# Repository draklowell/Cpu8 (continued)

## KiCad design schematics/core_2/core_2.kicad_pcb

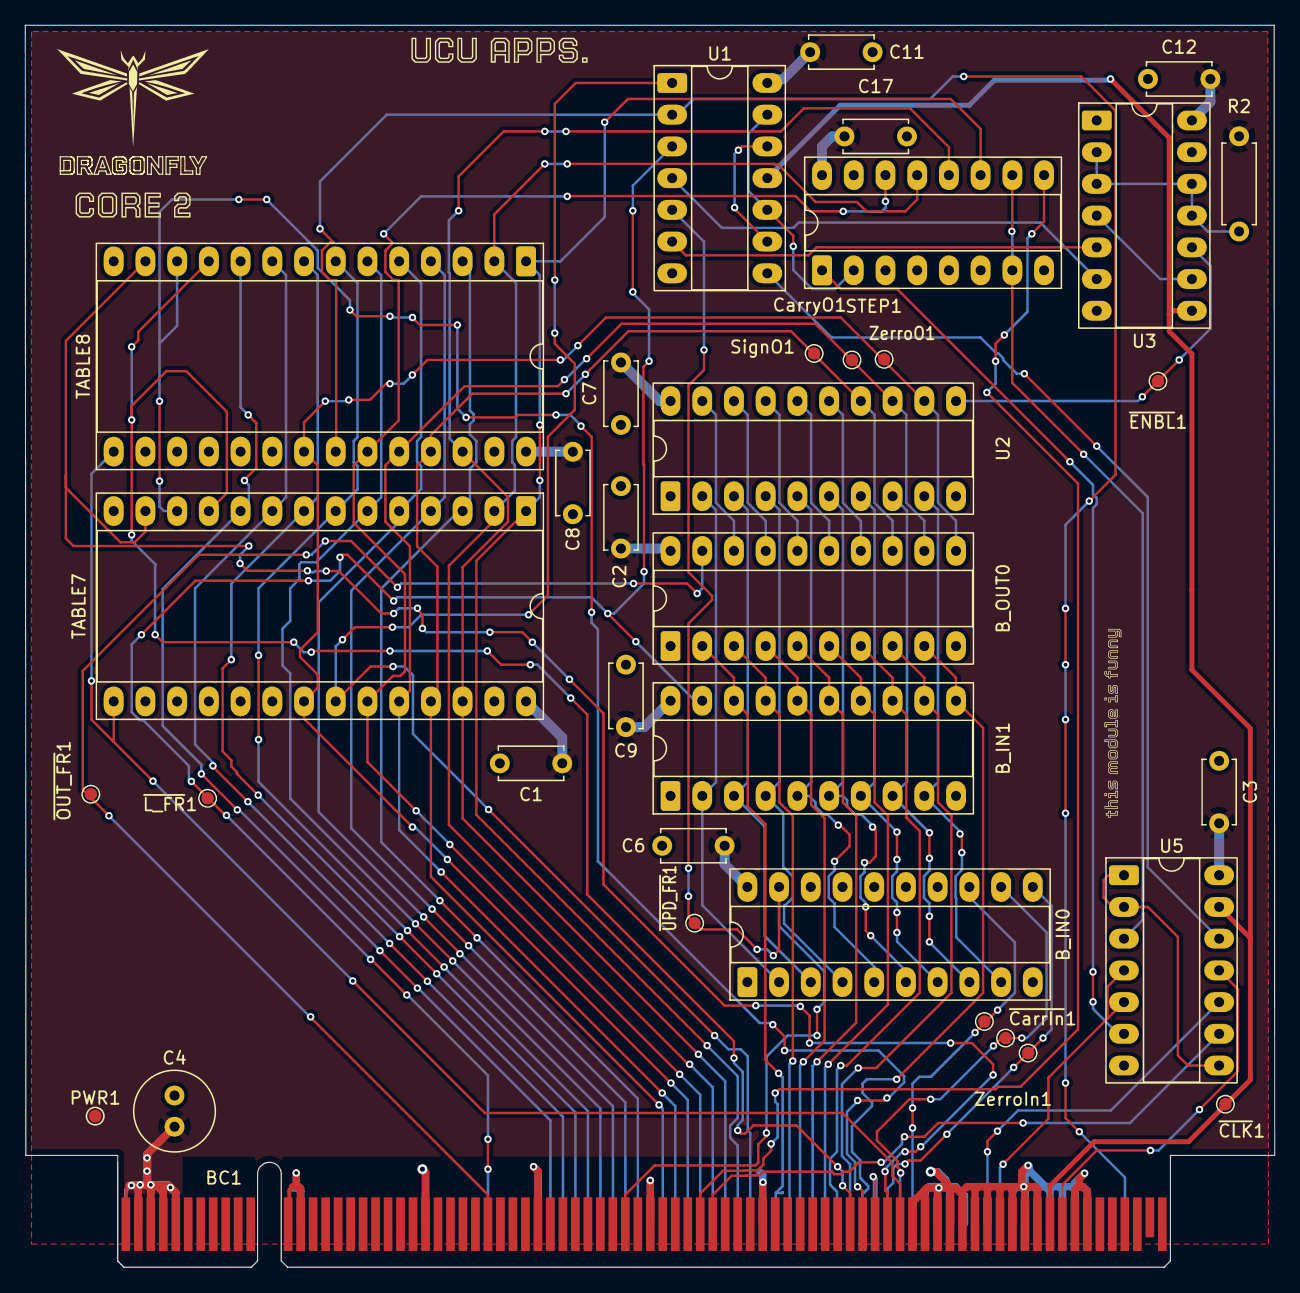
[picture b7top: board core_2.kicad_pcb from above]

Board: 2 copper layers, 100.0 x 99.5 mm, 31 parts (0 on the bottom side), 67 nets.

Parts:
BC1: BusConnector; BUS_PCIexpress_x16
B_IN0, B_IN1: 74LS245; DIP-20_W7.62mm_Socket_LongPads
B_OUT0: 74LS245; DIP-20_W7.62mm_Socket_LongPads
C1, C2, C3, C6, C7, C8, C9, C11, C12, C17: C; C_Disc_D5.0mm_W2.5mm_P5.00mm
C4: C; C_Radial_D6.3mm_H5.0mm_P2.50mm
CarryO1: TestPoint; TestPoint_Pad_D1.0mm
PWR1: TestPoint; TestPoint_Pad_D1.0mm
R2: R; R_Axial_DIN0207_L6.3mm_D2.5mm_P7.62mm_Horizontal
STEP1: 74LS161; DIP-16_W7.62mm_Socket_LongPads
SignO1: TestPoint; TestPoint_Pad_D1.0mm
TABLE7, TABLE8: 28C256; DIP-28_W15.24mm_Socket_LongPads
U1: 74LS04; DIP-14_W7.62mm_Socket_LongPads
U2: 74LS574; DIP-20_W7.62mm_Socket_LongPads
U3: 74LS02; DIP-14_W7.62mm_Socket_LongPads
U5: 74LS00; DIP-14_W7.62mm_Socket_LongPads
ZerroIn1: TestPoint; TestPoint_Pad_D1.0mm
ZerroO1: TestPoint; TestPoint_Pad_D1.0mm
kibuzzard-691DDE8A: G***; kibuzzard-691DDE8A
kibuzzard-691DE0EC: G***; kibuzzard-691DE0EC
kibuzzard-6911C9E9: G***; kibuzzard-6911C9E9

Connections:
/AddrDecrement: BC1.B60 (ADRDEC), TABLE7.13 (D2), TABLE8.13 (D2)
/AddrIncrement: BC1.B61 (ADDRINC), TABLE7.15 (D3), TABLE8.15 (D3)
/Clk: STEP1.2 (CP), U1.10, U1.13
/D0: BC1.A51 (DATA0), B_IN1.18 (B0), B_OUT0.2 (A0)
/D1: BC1.A52 (DATA1), B_IN1.17 (B1), B_OUT0.3 (A1)
/D2: BC1.A53 (DATA2), B_IN1.16 (B2), B_OUT0.4 (A2)
/D3: BC1.A54 (DATA3), B_IN1.15 (B3), B_OUT0.5 (A3)
/D4: BC1.A55 (DATA4), B_IN1.14 (B4), B_OUT0.6 (A4)
/D5: BC1.A56 (DATA5), B_IN1.13 (B5), B_OUT0.7 (A5)
/D6: BC1.A57 (DATA6), B_IN1.12 (B6), B_OUT0.8 (A6)
/D7: BC1.A58 (DATA7), B_IN1.11 (B7), B_OUT0.9 (A7)
/IntEnable: BC1.B57 (INTE), TABLE7.11 (D0), TABLE8.11 (D0)
/Reset: BC1.A69 (RESET), U5.4, U5.5
/STATE0: BC1.A33 (STATE0), TABLE7.10 (A0), TABLE8.10 (A0)
/STATE1: BC1.A34 (STATE1), TABLE7.9 (A1), TABLE8.9 (A1)
/STATE2: BC1.A35 (STATE2), TABLE7.8 (A2), TABLE8.8 (A2)
/STATE3: BC1.A36 (STATE3), TABLE7.7 (A3), TABLE8.7 (A3)
/STATE4: BC1.A37 (STATE4), TABLE7.6 (A4), TABLE8.6 (A4)
/STATE5: BC1.A38 (STATE5), TABLE7.5 (A5), TABLE8.5 (A5)
/STATE6: BC1.A39 (STATE6), TABLE7.4 (A6), TABLE8.4 (A6)
/STATE7: BC1.A40 (STATE7), TABLE7.3 (A7), TABLE8.3 (A7)
/STATE8: BC1.A42 (STATE8), B_OUT0.13 (B5), SignO1.1, TABLE7.25 (A8), TABLE8.25 (A8), U2.14 (Q5)
/STATE9: BC1.A43 (STATE9), B_OUT0.12 (B6), CarryO1.1, TABLE7.24 (A9), TABLE8.24 (A9), U2.13 (Q6)
/STATE10: BC1.A44 (STATE10), B_OUT0.11 (B7), TABLE7.21 (A10), TABLE8.21 (A10), U2.12 (Q7), ZerroO1.1
/STATE11: BC1.A45 (STATE11), STEP1.14 (Q0), TABLE7.23 (A11), TABLE8.23 (A11)
/STATE12: BC1.A46 (STATE12), STEP1.13 (Q1), TABLE7.2 (A12), TABLE8.2 (A12)
/STATE13: BC1.A47 (STATE13), STEP1.12 (Q2), TABLE7.26 (A13), TABLE8.26 (A13)
/STATE14: BC1.A48 (STATE14), STEP1.11 (Q3), TABLE7.1 (A14), TABLE8.1 (A14)
/STATE15: BC1.A49 (STATE15), TABLE7.22 (~OE), U1.1
/STATE16: BC1.A79 (STATE16), TABLE8.22 (~OE), U1.2
/SignIn: BC1.A62 (ALUSO), B_IN0.13 (B5)
/ZeroIn: BC1.A60 (ALUZO), B_IN0.11 (B7), ZerroIn1.1
/~CLK: BC1.B73 (~CLK), U1.11, U3.8, U5.13
/~CarryIn: BC1.A61 (~ALUCO), B_IN0.12 (B6)
/~Halt: BC1.B46 (~HALT), U5.9
/~IntDisable: BC1.B58 (~INTD), TABLE7.12 (D1), TABLE8.12 (D1)
/~LOAD_FR: BC1.A28 (~LFR), B_IN1.19 (CE), U1.3
/~OUT_FR: BC1.B28 (~RFR), B_OUT0.19 (CE)
/~SCClear: BC1.B45 (~SCCLR), STEP1.9 (~PE)
/~UPDATE_FR: BC1.B39 (FRUpd), B_IN0.19 (CE), U1.5
/~Wait: BC1.A68 (~WAIT), U5.10
GND: BC1.A12 (GND), BC1.A13 (GND), BC1.A23 (GND), BC1.A32 (GND), BC1.A41 (GND), BC1.A50 (GND), BC1.A59 (GND), BC1.A63 (GND), BC1.A64 (GND), BC1.A65 (GND), BC1.A66 (GND), BC1.A70 (GND), BC1.A71 (GND), BC1.A72 (GND), BC1.A73 (GND), BC1.A74 (GND), BC1.A75 (GND), BC1.A76 (GND), BC1.B12 (GND), BC1.B13 (GND), BC1.B23 (GND), BC1.B32 (GND), BC1.B41 (GND), BC1.B50 (GND), BC1.B59 (GND), BC1.B62 (GND), BC1.B63 (GND), BC1.B64 (GND), BC1.B65 (GND), BC1.B66 (GND), BC1.B67 (GND), BC1.B68 (GND), BC1.B69 (GND), BC1.B70 (GND), BC1.B71 (GND), BC1.B72 (GND), BC1.B75 (GND), BC1.B76 (GND), B_IN0.1 (A->B), B_IN0.10 (GND), B_IN0.14 (B4), B_IN0.15 (B3), B_IN0.16 (B2), B_IN0.17 (B1), B_IN0.18 (B0), B_IN1.1 (A->B), B_IN1.10 (GND), B_OUT0.1 (A->B), B_OUT0.10 (GND), C1.2, C2.2, C3.2, C4.2, C6.1, C7.1, C8.1, C9.1, C11.2, C12.2, C17.2, STEP1.3 (D0), STEP1.4 (D1), STEP1.5 (D2), STEP1.6 (D3), STEP1.8 (GND), TABLE7.14 (GND), TABLE7.20 (~CS), TABLE7.27 (~WE), TABLE8.14 (GND), TABLE8.20 (~CS), TABLE8.27 (~WE), U1.7 (GND), U2.1 (OE), U2.10 (GND), U3.7 (GND), U5.7 (GND)
unnamed: BC1.B74 (PULSE), U5.11
unnamed: B_IN0.2 (A0), B_IN1.2 (A0), U2.2 (D0)
unnamed: B_IN0.3 (A1), B_IN1.3 (A1), U2.3 (D1)
unnamed: B_IN0.4 (A2), B_IN1.4 (A2), U2.4 (D2)
unnamed: B_IN0.5 (A3), B_IN1.5 (A3), U2.5 (D3)
unnamed: B_IN0.6 (A4), B_IN1.6 (A4), U2.6 (D4)
unnamed: B_IN0.7 (A5), B_IN1.7 (A5), U2.7 (D5)
unnamed: B_IN0.8 (A6), B_IN1.8 (A6), U2.8 (D6)
unnamed: B_IN0.9 (A7), B_IN1.9 (A7), U2.9 (D7)
unnamed: B_OUT0.18 (B0), U2.19 (Q0)
unnamed: B_OUT0.17 (B1), U2.18 (Q1)
unnamed: B_OUT0.16 (B2), U2.17 (Q2)
unnamed: B_OUT0.15 (B3), U2.16 (Q3)
unnamed: B_OUT0.14 (B4), U2.15 (Q4)
unnamed: R2.2, U3.2, U3.3, U3.11, U3.12
unnamed: STEP1.7 (CEP), STEP1.10 (CET), U5.3
unnamed: STEP1.1 (~MR), U5.6
unnamed: U1.4, U3.6
unnamed: U1.6, U3.5
unnamed: U1.8, U5.12
unnamed: U1.9, U1.12
unnamed: U2.11 (Cp), U3.10
unnamed: U3.4, U3.9
unnamed: U5.1, U5.2, U5.8
VCC: BC1.A1 (VCC), BC1.A2 (VCC), BC1.A3 (VCC), BC1.A4 (VCC), BC1.A5 (VCC), BC1.B1 (VCC), BC1.B2 (VCC), BC1.B3 (VCC), BC1.B4 (VCC), BC1.B5 (VCC), B_IN0.20 (VCC), B_IN1.20 (VCC), B_OUT0.20 (VCC), C1.1, C2.1, C3.1, C4.1, C6.2, C7.2, C8.2, C9.2, C11.1, C12.1, C17.1, PWR1.1, R2.1, STEP1.16 (VCC), TABLE7.28 (VCC), TABLE8.28 (VCC), U1.14 (VCC), U2.20 (VCC), U3.14 (VCC), U5.14 (VCC)

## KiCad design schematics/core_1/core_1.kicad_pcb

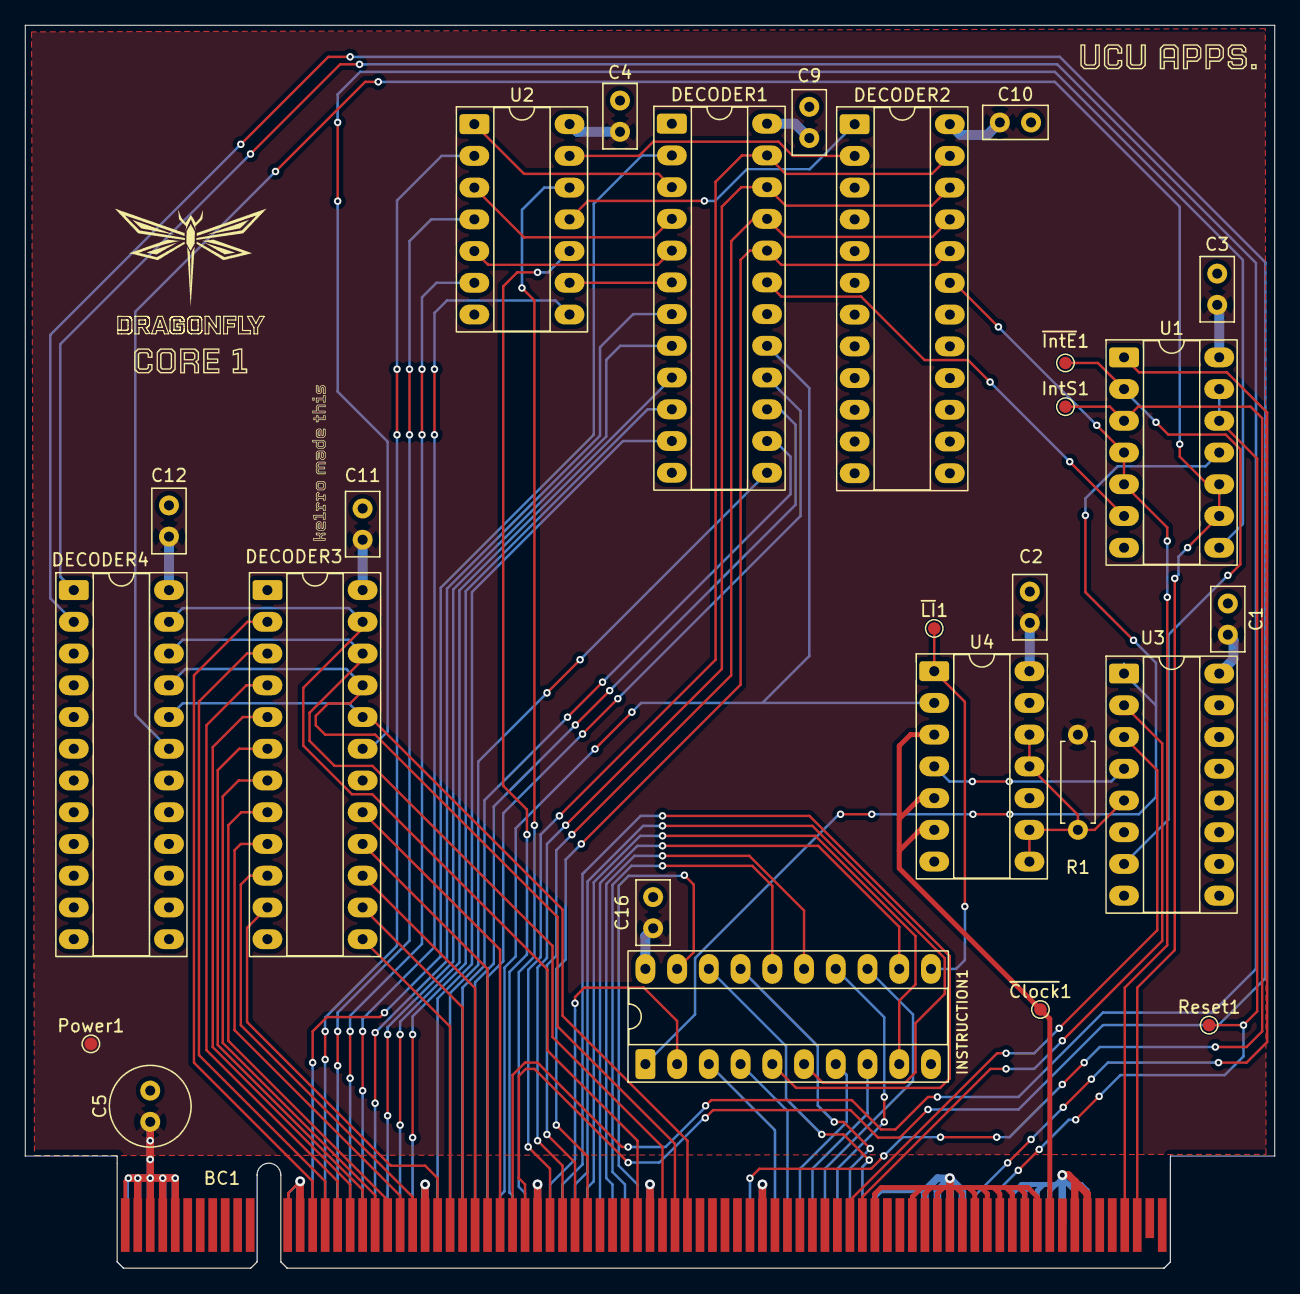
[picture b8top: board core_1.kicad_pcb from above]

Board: 2 copper layers, 100.0 x 99.5 mm, 27 parts (0 on the bottom side), 81 nets.

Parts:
BC1: BusConnector; BUS_PCIexpress_x16
C1, C2, C3, C4, C9, C10, C11, C12, C16: C; C_Disc_D5.0mm_W2.5mm_P2.50mm
C5: C; C_Radial_D6.3mm_H5.0mm_P2.50mm
DECODER1, DECODER2, DECODER3, DECODER4: 74LS154; DIP-24_W7.62mm_Socket_LongPads
INSTRUCTION1: 74LS273; DIP-20_W7.62mm_Socket_LongPads
IntS1: IntS; TestPoint_Pad_D1.0mm
Power1: Power; TestPoint_Pad_D1.0mm
R1: 5kOhm; R_Axial_DIN0207_L6.3mm_D2.5mm_P7.62mm_Horizontal
Reset1: Reset; TestPoint_Pad_D1.0mm
U1: 74LS00; DIP-14_W7.62mm_Socket_LongPads
U2: 74LS04; DIP-14_W7.62mm_Socket_LongPads
U3: 74LS109; DIP-16_W7.62mm_Socket_LongPads
U4: 74LS02; DIP-14_W7.62mm_Socket_LongPads
kibuzzard-691DE05D: G***; kibuzzard-691DE05D
kibuzzard-691DE084: G***; kibuzzard-691DE084
kibuzzard-6911CC41: G***; kibuzzard-6911CC41

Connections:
/AddrHighIn: BC1.A30 (LADRH), U2.10
/AddrLowIn: BC1.A31 (LADRL), U2.12
/BUS0: BC1.A51 (DATA0), INSTRUCTION1.3 (D0)
/BUS1: BC1.A52 (DATA1), INSTRUCTION1.4 (D1)
/BUS2: BC1.A53 (DATA2), INSTRUCTION1.7 (D2)
/BUS3: BC1.A54 (DATA3), INSTRUCTION1.8 (D3)
/BUS4: BC1.A55 (DATA4), INSTRUCTION1.13 (D4)
/BUS5: BC1.A56 (DATA5), INSTRUCTION1.14 (D5)
/BUS6: BC1.A57 (DATA6), INSTRUCTION1.17 (D6)
/BUS7: BC1.A58 (DATA7), INSTRUCTION1.18 (D7)
/IRQ: BC1.A67 (INTREQ), U1.1
/IntEnable: BC1.B57 (INTE), U3.3 (~K)
/L0: BC1.B33 (L0), DECODER1.23 (A0), DECODER2.23 (A0)
/L1: BC1.B34 (L1), DECODER1.22 (A1), DECODER2.22 (A1)
/L2: BC1.B35 (L2), DECODER1.21 (A2), DECODER2.21 (A2)
/L3: BC1.B36 (L3), DECODER1.20 (A3), DECODER2.20 (A3)
/L4: BC1.B79 (L4), DECODER2.19 (E1), U1.4, U1.5
/PCHighReader: BC1.A17 (LPCH), U2.6
/PCLowReader: BC1.A18 (LPCL), U2.8
/R0: BC1.B40 (R0), DECODER3.23 (A0), DECODER4.23 (A0)
/R1: BC1.B42 (R1), DECODER3.22 (A1), DECODER4.22 (A1)
/R2: BC1.B43 (R2), DECODER3.21 (A2), DECODER4.21 (A2)
/R3: BC1.B44 (R3), DECODER3.20 (A3), DECODER4.20 (A3)
/R4: BC1.B80 (R4), DECODER4.19 (E1), U1.9, U1.10
/Reset: BC1.A69 (RESET), Reset1.1, U1.12, U1.13
/SPHighReader: BC1.A15 (LSPH), U2.2
/SPLowReader: BC1.A16 (LSPL), U2.4
/STATE0: BC1.A33 (STATE0), INSTRUCTION1.2 (Q0)
/STATE1: BC1.A34 (STATE1), INSTRUCTION1.5 (Q1)
/STATE2: BC1.A35 (STATE2), INSTRUCTION1.6 (Q2)
/STATE3: BC1.A36 (STATE3), INSTRUCTION1.9 (Q3)
/STATE4: BC1.A37 (STATE4), INSTRUCTION1.12 (Q4)
/STATE5: BC1.A38 (STATE5), INSTRUCTION1.15 (Q5)
/STATE6: BC1.A39 (STATE6), INSTRUCTION1.16 (Q6)
/STATE7: BC1.A40 (STATE7), INSTRUCTION1.19 (Q7)
/~ALUWriter: BC1.B30 (~RALU), DECODER4.1 (S0)
/~AccumReader: BC1.A21 (~LAC), DECODER1.9 (S8)
/~AccumWriter: BC1.B21 (~RAC), DECODER3.9 (S8)
/~AddressHighReader: DECODER2.1 (S0), U2.11
/~AddressLowReader: DECODER2.2 (S1), U2.13
/~Clk: BC1.B73 (~CLK), U4.3, U4.5, U4.6
/~ConstantWriter: BC1.B29 (~RCONST), DECODER3.17 (S15)
/~FlagsReader: BC1.A28 (~LFR), DECODER1.16 (S14)
/~FlagsWriter: BC1.B28 (~RFR), DECODER3.16 (S14)
/~InstructionReader: BC1.A29 (~LINST), DECODER1.17 (S15), U4.2
/~IntAck: BC1.B31 (~RINTC), DECODER4.2 (S1)
/~IntDisable: BC1.B58 (~INTD), U3.2 (J)
/~MemoryReader: BC1.A14 (~LMEM), DECODER1.2 (S1)
/~MemoryWriter: BC1.B14 (~RMEM), DECODER3.2 (S1)
/~PCHighReader: DECODER1.5 (S4), U2.5
/~PCHighWriter: BC1.B17 (~RPCH), DECODER3.5 (S4)
/~PCLowReader: DECODER1.6 (S5), U2.9
/~PCLowWriter: BC1.B18 (~RPCL), DECODER3.6 (S5)
/~Reset: INSTRUCTION1.1 (~Mr), U1.11, U3.1 (~R)
/~SPHighReader: DECODER1.3 (S2), U2.1
/~SPHighWriter: BC1.B15 (~RSPH), DECODER3.3 (S2)
/~SPLowReader: DECODER1.4 (S3), U2.3
/~SPLowWriter: BC1.B16 (~RSPL), DECODER3.4 (S3)
/~TemporaryHighReader: BC1.A19 (~LARGH), DECODER1.7 (S6)
/~TemporaryHighWriter: BC1.B19 (~RARGH), DECODER3.7 (S6)
/~TemporaryLowReader: BC1.A20 (~LARGL), DECODER1.8 (S7)
/~TemporaryLowWriter: BC1.B20 (~RARGL), DECODER3.8 (S7)
/~XHReader: BC1.A22 (~LXH), DECODER1.10 (S9)
/~XHWriter: BC1.B22 (~RXH), DECODER3.10 (S9)
/~YHReader: BC1.A25 (~LYH), DECODER1.13 (S11)
/~YHWriter: BC1.B25 (~RYH), DECODER3.13 (S11)
/~YLReader: BC1.A24 (~LYL), DECODER1.11 (S10)
/~YLWriter: BC1.B24 (~RYL), DECODER3.11 (S10)
/~ZHReader: BC1.A27 (~LZH), DECODER1.15 (S13)
/~ZHWriter: BC1.B27 (~RZH), DECODER3.15 (S13)
/~ZLReader: BC1.A26 (~LZL), DECODER1.14 (S12)
/~ZLWriter: BC1.B26 (~RZL), DECODER3.14 (S12)
GND: BC1.A12 (GND), BC1.A13 (GND), BC1.A23 (GND), BC1.A32 (GND), BC1.A41 (GND), BC1.A50 (GND), BC1.A59 (GND), BC1.A63 (GND), BC1.A64 (GND), BC1.A65 (GND), BC1.A66 (GND), BC1.A70 (GND), BC1.A71 (GND), BC1.A72 (GND), BC1.A73 (GND), BC1.A74 (GND), BC1.A75 (GND), BC1.A76 (GND), BC1.B12 (GND), BC1.B13 (GND), BC1.B23 (GND), BC1.B32 (GND), BC1.B41 (GND), BC1.B50 (GND), BC1.B59 (GND), BC1.B62 (GND), BC1.B63 (GND), BC1.B64 (GND), BC1.B65 (GND), BC1.B66 (GND), BC1.B67 (GND), BC1.B68 (GND), BC1.B69 (GND), BC1.B70 (GND), BC1.B71 (GND), BC1.B72 (GND), BC1.B75 (GND), BC1.B76 (GND), C1.2, C2.2, C3.2, C4.2, C5.2, C9.2, C10.2, C11.2, C12.2, C16.2, DECODER1.12 (GND), DECODER1.18 (E0), DECODER2.12 (GND), DECODER2.18 (E0), DECODER3.12 (GND), DECODER3.18 (E0), DECODER4.12 (GND), DECODER4.18 (E0), INSTRUCTION1.10 (GND), U1.7 (GND), U2.7 (GND), U3.8 (GND), U3.15 (~R), U4.7 (GND)
unnamed: BC1.A49 (STATE15), IntS1.1, U1.3
unnamed: DECODER1.19 (E1), U1.6
unnamed: DECODER3.19 (E1), U1.8
unnamed: INSTRUCTION1.11 (Cp), U4.1
unnamed: U3.4 (C), U4.4
unnamed: U1.2, U3.7 (~Q)
unnamed: R1.2, U3.5 (~S), U4.8, U4.9, U4.11, U4.12
VCC: BC1.A1 (VCC), BC1.A2 (VCC), BC1.A3 (VCC), BC1.A4 (VCC), BC1.A5 (VCC), BC1.B1 (VCC), BC1.B2 (VCC), BC1.B3 (VCC), BC1.B4 (VCC), BC1.B5 (VCC), C1.1, C2.1, C3.1, C4.1, C5.1, C9.1, C10.1, C11.1, C12.1, C16.1, DECODER1.24 (VCC), DECODER2.24 (VCC), DECODER3.24 (VCC), DECODER4.24 (VCC), INSTRUCTION1.20 (VCC), Power1.1, R1.1, U1.14 (VCC), U2.14 (VCC), U3.16 (VCC), U4.14 (VCC)

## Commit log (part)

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2024-10-09 more convenient file structure
2024-10-09 gitignore
2024-10-09 .idea cleaned
2024-10-10 examples
2024-10-22 ALU logisim-evo rewrite
2024-10-22 rom reader
2024-10-23 add registers
2024-10-23 add </circuit>
2024-10-23 fix registers
2024-10-23 added registers tunnels
2024-10-23 fix registers + add some intermediate logic
2024-10-23 minor fix
2024-10-23 hot f(d)ix v2
2024-11-05 slightly better readme
2024-11-05 jumps
2024-11-05 readme
2024-11-05 meow
2024-11-05 smaller scheme
2024-11-12 IO reads data from registers
2024-11-13 added HALT operation with code 1000
2024-11-13 fixed registers
2024-11-21 jumps ready
2024-11-21 normal interrupts
2024-12-06 translator
2024-12-08 general test asm code
2024-12-12 added proteus CPU simulation and bin files for its ROM and op decoder
2025-09-23 Remake ProgramCounter with other counter for raising-edge behavior
2025-09-29 Reimplement CPU, reduce control bus and remake microassembler
2025-09-29 Add todo comment
2025-10-04 feat(docs): add initial documentation for ASM structures and operand types
2025-10-04 feat(structure): ASM structures and operand types, .gitignore, cmake(temp)
2025-10-04 feat(docs): enhance documentation for ASM structures, symbol table, and relocation system feat(asm): implement Pass1 and Pass2 classes for assembler functionality feat(asm): add Parser class for asse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
2025-10-05 Fix interrupts and make intack a component of bus
2025-10-05 Add PVS-Studio comments and generate opcode tables
    - Added comments to source files indicating this is a personal academic project and a request for PVS-Studio analysis.
    - Introduced a new script `gen_encode_table.py` to generate an opcode table from `table.txt`.
    - Created `EncodeTable.inc.hpp` to store generated opcode definitions.
    - Added `table.txt` and `table_hp.txt` containing opcode definitions for the assembler.
    - Updated header files to include the new comments.
2025-10-05 chore(cpu): updated gitignore with C++ template
2025-10-05 Fix duplicated operations on Y registers
2025-10-05 fix(instrencoding): fixed ldi16
2025-10-05 chore: add .PVS-Studio to .gitignore
2025-10-05 added emulator base structure
2025-10-06 temp commit
2025-10-06 Fix bug on next operation loading under interrupt, remove constant in instruction decoder
2025-10-08 Add basic README and assets
2025-10-10 chore(asm): added example file
2025-10-13 feat(directives): added Directives suports
2025-10-15 feat(Symbol table): added functionality to symtab + string recognition to parser
2025-10-16 feat: implemented pass1, fixed public in directives.hpp
2025-10-16 fix(structure ): removed redundant file
2025-10-16 feat(asm): Implemented simple asm compiler for 1 object file added Example and bin for example
2025-10-17 fix(pass2): added helper methods to exctract opdoces for register dependant instructions
2025-10-17 chore(test files): added example files with gcc preprocessor usage
2025-10-18 baseline working emulator
2025-10-19 added register file hub
2025-10-19 Added pointerhub + basecouter sch
2025-10-23 Add main_hub
2025-10-23 Clean unnecessary files
2025-10-23 feat(kicad): added alu hub, combined accumulator, argument register, alu from logisim-evolution
2025-10-23 fix(kicad): errors related with high args
2025-10-24 fix(kicad): updated footprints
2025-10-24 added zip
2025-10-24 added kicad files
2025-10-24 feat(asm): moved reusable methods to registerdependent code added examples for emu and all
2025-10-24 fixed all errors
2025-10-24 fix(kicad): fixed kicad ERC errors, replaces resistors to capacitors
2025-10-24 Add more labels to main hub decoder
2025-10-24 Connnect all modules together
2025-10-25 added lowarg to pointerhub, also replaced resistor + vcc logic by grnd and changing A and B pins(A was in became out...)
2025-10-25 fix: added kicad gitignore
2025-10-25 chore(documentation): added docuementation about syntax to assembler CPU8/16
2025-10-25 Add interface module schematic
2025-10-25 chore(kicad): added pdfs directory for schematics
2025-10-25 Refactor and enhance assembler toolchain
    - Added Serializer class for file operations in `Serializer.hpp`.
    - Removed obsolete test files (`test.S`, `test2.S`, `test_mini.s`) to clean up the project.
    - Introduced comprehensive documentation for the CPU8/16 assembler in `ASM_DOCUMENTATION.md`.
    - Created detailed `DOCUMENTATION.md` outlining operand types, registers, symbol tables, and error types.
    - Added multiple example programs to demonstrate assembler functionality and instruction coverage.
    - Implemented a full test program (`ExampleALL_Emu.s`) exercising all mnemonics from the instruction set.
2025-10-25 feat(link): implement Linker, RelocResolver, and SectionMerger with associated structures and methods
2025-10-25 refactor(build): restructure CMakeLists and add new CLI tools for assembler and linker
2025-10-25 feat(build): update CMakeLists to define ASM_SOURCES and ASM_HEADERS for executables feat(docs): add opcode verification report for main.s and sum.s fix(ld_cli): correct include paths and change main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
2025-10-26 feat(link): enhance symbol resolution to include relocatable status
2025-10-26 docs: update ASM documentation with CLI utilities and remove obsolete report
2025-10-26 docs: clarify error message for loading 16-bit values into 8-bit registers
2025-10-27 feat: update CMake configuration, add new CLI tools, and enhance documentation
2025-10-27 copy gitignore from remote.
2025-10-28 refactor: error messages
2025-10-31 split rf into rf and core 1
2025-10-31 (feat) sp and pc added
2025-10-31 Add backplane connector symbol
2025-10-31 Update connector
2025-10-31 Fix labels
2025-10-31 Add gen2 base module and interface module
2025-10-31 feat: Alu hub + pdfs
2025-10-31 (feat) step_counter update.
2025-11-01 fix: update accumulator schematic and routing rules
2025-11-01 implemented pcb for register file
2025-11-02 feat: alu hub + pcb base not finished yet
2025-11-02 pc and sp sch
2025-11-02 feat(alu): added vcc and gnd back plate
2025-11-04 (feat) stack pointer and program counter pcb, QA needed.
2025-11-04 feat: added gnd connections for alu hub
2025-11-04 fix: changed the placement
2025-11-04 feat: alu hub
2025-11-04 fix: changed footprints in accum, added resistor and capacitor footrpint
2025-11-05 fix(accum): update segment connections and adjust routing
2025-11-07 stack rework
2025-11-07 remake of register file module
2025-11-07 Add gen2/core_2
2025-11-07 fixed errors
2025-11-07 added sym table
2025-11-07 refactor(accum): reimplemented accumalot module
2025-11-07 Add core_3
2025-11-07 Add core3, fix core2
2025-11-07 program counter complete
2025-11-07 fixed bugs in core 1 sch
2025-11-08 feat(alu): add resistor symbol and connections to ALU hub schematic
2025-11-08 alu hub done
2025-11-08 almost ready core 2
2025-11-08 doine(core_ 2): almost ready to print
2025-11-08 core1 completed
2025-11-09 inprogress(interface): 19 pins left
2025-11-09 upd: changed logo to svg + svg
2025-11-10 design + fix core_2
2025-11-10 fix(register file): added pull up resistor fixed schematic, changed capacitors
2025-11-10 fix clk in core_1
2025-11-10 accum review complete
2025-11-10 accum review complete final
2025-11-10 fix(pc): changed resistor, capacitors footprints
2025-11-10 fix(stack pointer): fixed footprints
2025-11-10 alu review
2025-11-10 chore(accum): changed logo and text
2025-11-10 chore(core 2): changed logo and text
2025-11-10 interface review
2025-11-10 chore(core 1): added logo and text
2025-11-10 chore(kicad-pcb): added apps ucu logo
2025-11-10 Add core 3
2025-11-10 fix(kicad): vcc zones
2025-11-10 register_file
2025-11-11 Add backplane
2025-11-12 combine accum and reg_file
2025-11-12 fix(alu): deleted copy file
2025-11-12 Remove unused modules
2025-11-12 added showcase preview
2025-11-12 silklayer check
2025-11-12 Update backplane, add power supply and debug port
2025-11-13 tried to make core_3
2025-11-15 feat: add cpu_objdump executable and implement object file reading
2025-11-15 fix(alu): changed vcc gnd connection + clearence of cooper zones
2025-11-15 power change
2025-11-15 fix(core2): changed vcc and gnd connection + cooper clearence
2025-11-16 chore(alu): deleted redundant module
2025-11-16 fix: removed in control pins daisy chains
2025-11-16 fix(backplane): changed vcc and gnd connector
2025-11-17 Add pcb for core 3
2025-11-17 fix(backplane): removed duplicates of zones
2025-11-17 fix(alu): vcc conn
2025-11-19 fix(register_accum): fixed the data to y shape connection removed the vcc from the resistor
2025-11-19 added testpoints on core 2
2025-11-19 Add test points
2025-11-19 Add test points in Core 1
2025-11-19 slight changes to vcc
2025-11-19 upd(installation): updated docs for installation and uninstallation
2025-11-19 slight changes
2025-11-19 update pc and sp
2025-11-19 fix(alu, interface): fix tp
2025-11-19 test points sp and pc
2025-11-19 Add test points for register file + accum
2025-11-19 final review
2025-11-19 done
2025-11-20 feat(gerbers): made order in jlcpcb and fixed document
2025-12-07 Actualize logisim and microcode to actual physical implementation of the CPU
2025-12-08 Add table generator to microcode
2025-12-29 chore: deleted python emulator, depracated schematics, moved dragonfly logo to assets, moved asm code to asm_toolchain/examples directory
2026-01-06 New version of logisim
2026-01-07 Push periphery and fix schematics
2026-01-07 wip: base of simulator
2026-01-07 implemented IC logic
2026-01-07 Add interface
2026-01-07 Fix conflict
2026-01-07 Fix imports
2026-01-07 Remove test runner
2026-01-08 Update simulator
2026-01-08 Fixed some bugs
2026-01-08 Fix hierarchy
2026-01-09 Add log printing
2026-01-09 Make api more convenient (pins are not exposed directly, but via aliases)
2026-01-09 Fix pinouts and aliases
2026-01-09 Add enhanced simulate usage
2026-01-10 fix(debug.ino): fixed alignment in output str
2026-01-10 Fix microcode
2026-01-10 Enhance simulate.py
2026-01-10 Fix U4 connection in interface
2026-01-10 Fix reading from memory
2026-01-10 Fix TC floating
2026-01-10 Fix borrow and carry in ic 74193 (floating when not counting, but has to be high)
2026-01-10 Fix inverted pulse
2026-01-10 Implement 74573 ic
2026-01-10 Fix pulse detector
2026-01-10 Fix addressing in stack and add halt condition in simulator
2026-01-11 Add logging instruction mnemonics
2026-01-11 fix(asm examples): changed entry points + fixed bug
2026-01-11 Fix reader and writer recognition
2026-01-11 Add kiri artefacts to gitignore
2026-01-11 feat(simulator/export): added compatibility with kicad-cli and fontconfig for darwin users
2026-01-11 fix(export): fixed path to kicad
2026-01-11 feat(gdb-dragonfly): added watch component
2026-01-11 feat(gdb-dragonfly): added base ui elements for future cli
2026-01-11 feat(gdb-dragonfly): state of cpu to track, breakpoints functionality for gdb
2026-01-11 feat(gdb-dragongly): added diasm functionality
2026-01-11 feat(gdb-dragonfly): gdb cli
2026-01-11 feat(gdb test): added test for cli and functionality
2026-01-11 feat(test): added test for pushes and prs into schematics and simulator
2026-01-11 chore: deleted not related files
2026-01-11 fix(ci): added mkdir for bin/
2026-01-11 fix: moved docs from tests
2026-01-11 fix(gdb): run isort + black
2026-01-12 fix(gdb-test): moved to another dir
2026-01-13 chore(tests): moved manual tests into tests directory
2026-01-13 fix(config): fixed vars name conflict , added cycles constant
2026-01-15 Remake with ic74373
2026-01-15 Update periphery to output csv
2026-01-15 Fix pinout for debug port
2026-01-15 Rewrite logging for periphery
2026-01-15 Fix operation detection
2026-01-15 Fix periphery
2026-01-16 feat(periphery): added script to write uart data to file
2026-01-16 test: made snapshot for different sources
2026-01-16 Repair dumps and add merging mechanism to create waveforms
2026-01-16 Add simulation to vcd file
2026-01-19 added tests
2026-01-19 added test
2026-01-19 log port luka
2026-01-19 Add merged logs
2026-01-19 maybe victory
2026-01-19 more_tests
2026-01-19 debug 8
2026-01-19 add test
2026-01-19 add 9 test
2026-01-19 add 10, 11 test
2026-01-19 debug bulk
2026-01-19 Add merged vcds
